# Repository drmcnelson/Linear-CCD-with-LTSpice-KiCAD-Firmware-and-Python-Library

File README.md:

# Linear-CCD-with-LTSpice-KiCAD-Firmware-and-Python-Library
by Dr M C Nelson (C) 20220-2026 [(the authoritative repo is here)](https://github.com/drmcnelson/Linear-CCD-with-LTSpice-KiCAD-Firmware-and-Python-Library)

<br>

> **Note:** For the **high-linearity version** for quantitative science along with a revised implementation of this all-in-one design but now with hardware locked timing (using the FlexPWM), please see the newer repository: [TCD1304-Sensor-Device-with-Linear-Response-and-16-Bit-Differential-ADC](https://github.com/drmcnelson/TCD1304-Sensor-Device-with-Linear-Response-and-16-Bit-Differential-ADC).

<br>

## Introduction
Linear CCDs can be useful tools in science, for example as a sensor for a spectrometer or imaging system.  And indeed, there are many commercial instruments that are based on low cost linear CCDs such as the Toshiba TC1304 and the Sony IXL511.
Here we provide design files, firmware and software for a device that provides competitive performance and a rich set of science-centric features, and that can be customized to your experiments, all at a fraction of the cost of the commercial offerings.  The design is based on the Toshiba TCD1304 (3648/3694 pixels) and Teensy 4.0 (600MHz ARM, 480MHz USB).  The Teensy 3.2 is plug compatible for this design.
Read further below, and you will find tutorials on electrical design and managing the CCD to provide flexible timing and reproducible measurements so that you can use it as a scientific instrument.

In this repository you will find directories containing (a) electrical design files in KiCad, (b) firmware (a sketch file) for the Teensy, and (c) a Python class library with graphical and command line utilities to operate the device.
The device has a trigger or gate input, sync and busy outputs, and spare pins for digital and analog I/O.
The operating modes include clocked, triggered frames, triggered series of frames, and gated frames (where the shutter is opened and closed on the rising and falling edges of the logic level input signal).
The device appears as a serial port (COM in windows) with comands and response in human language ASCII and frames returned as binary or formatted.
The python class library provides higher level functions, a graphical realtime display and a command line processor.  There is a help command in the firmware and in the Python command line interpreter.  Details of the electrical and firmware design are described later in this README.

The following shows the microcontroller side of the device.  The sensor side can be seen in the image of the spectrometer (below).   The digital I/O pins across the top include trigger input, sync and busy output, pins that monitor the signals going to the sensor, and spares that can be controlled through the user interface.  Across the bottom there are pins that can be used for analog inputs or digital I/O, and 3.3V that can be used for an auxiliary device.

Following are two examples of applications; using the sensor in a spectrometer and measurement of spectral-spatial-dynamics in an OLED.  This repository provides what you need in terms of ecad files and software to build one for yourself, or if you like you can contact me for an assembled board.

The files in the repo were produced on a Linux desktop computer (Fedora 37, Cinnamon Spin), using KiCAD 6 for the electrical design and Emacs for the firmware and python programs.

<ul>
 <i>
For next level designs and a preview of our study on linearity and reproducibility in CCDs see our new repo at <a href=https://github.com/drmcnelson/TCD1304-Sensor-Device-with-Linear-Response-and-16-Bit-Differential-ADC>TCD1304 with linear response and 16bit ADC</a>. We suggest perusing both this and the new repo and selecting the implementation that best serves your needs.  Feel free to contact me with questions.
 </i>
</ul>

## Some Example Use Cases

### Spectrometer
The first shows the inside of a spectrometer built with a G1200 grating, two lenses and a slit. The mounts are 3D printed and everything is affixed to a stiff Al plate. There is a cover, not shown here, and specific surfaces are covered with low-reflectance tape.  The spectrum is that of a fluorescent ceiling light through a 200um fiber at a distance of about 8ft, with a 200um slit.

|||

### Imaging Spectral-Spatial-Dynamics
The following example uses the sensor device to record the time evolution of the spatial distribution of light produced by an OLED at a current density of 150 $\mu A/cm^2$. The sensor device collects a series of frames wth 10ms shutters at 10ms intervals (back to back), with the series initated on a trigger at the start of the applied voltage waveform. The blue line shows the resulting current density in the OLED, the pale line shows the sync pulses output by the sensor device at the start of each frame, and the red line is the applied voltage (2.41V).  (We plan to post repositories for the DAQ board and current amplifier as well.)

|||

# Electrical Design, Analog
The datasheet for the TCD1304 can be found here  https://toshiba.semicon-storage.com/us/semiconductor/product/linear-image-sensors/detail.TCD1304DG.html.
The following table is found on page 4.
We see that $V_{SAT}$ the saturation output volage runs from 450mV to 600mV, $V_{MDK}$ the dark signal is 2mV, thus a dynamic range of 300 (for a 10ms integration integral), $V_{OS}$ the DC output signal is typically 2.5V but can be from 1.5V to 3.5V, and $Z_O$ the output impedance is typically 500 ohms but can be 1K.  So, that is a lot of variation that we need to account for in our design.

The datasheet provides the following diagram in Note 8 to illustrate the definition of $V_{OS}$.  The hatched area is the negative going output signal.  SS is ground

For best performance in digitizing the signal, we want a circuit that takes the above signal as input and outputs a signal that matches the input range of our microcontroller's ADC.  The following circuit element shows one approach that does this and can run on a single supply. We can call this a shift, flip and amplify (SFA). The gain is set as usual for an inverting amplifier by $R_2$ and $R_1$ and the potentiometer provides the offset through the + input of the opamp.

But, recall that the datasheet says the output impedance $Z_0$ varies from 500 ohms to 1k.  If we connect that directly to our SFA then $Z_0$ becomes part of the gain equation, $R1\rightarrow R1+Z_0$, and in a bag of sensors we might find that the gain is different for each sensor.
So, we need to isolate that source impedance from the SFA.

A solution to this is to use an opamp follower as the first stage, as shown in the following crcuit.  The follower presents a very high impedance at its input, which is ideal for reading the voltage from the sensor, and a low impedance at its output, which is ideal as an input to the SFA

Referring again to the datasheet for the TCD1304, we see that (a) we can operate the sensor chip in the range 3V to 5.5V, (b) it requires a clock between 800KHz and 4MHz (2MHz if operated below 4V) and (c) the data readout rate is 1/4 of the clock 200kS/s to 1MS/s (500KS/S if powered below 4V).
Operating with a 3.3V supply, and making efficient use of the full scale range of the ADC,  means that we need to use a rail to rail opamp.
Our SFA architecture means that the opamp has to also have a wide common mode range. 
And the sampling rate means we need to look for a slew at least as faster as 100V/usec

The complete analog front end circuit is shown in the following LTSpice model based on the ADA4807.
We use the first opamp in the package for the voltage follower and the second opamp for the flip, shift,and amplify stage.
Gain and offset are as calculated above.
The green trace is the output from the sensor and the purple curve is the output from the second stage.
As can be seen the 2.5V to 1.9V signal from the sensor becomes a 0.1V to 3.1V for the ADC, and the rise time is small compared to the sampling period.
In our actual circuit we use a trim pot for the voltage applied to V+.

It might be noted that we could have chosen a larger gain to look at lower intensity light, or with the Teensy 3.2 we can use its built-in amplifier under software control, provided the offset is small.

## Analog input of the Teensy 4.x and Teensy 3.2
The following diagaram for the analog input, and one similar to this, are found in the datasheets for the i.MXRT106x (Teensy 4) and the K20 (Teensy 3).
This is a modified version of a SAR type analog input.  Normally the input sees the switched sampling capacitor.
Here there is a series resistor in front of the sampling capacitor.

In operation, the switch closes for a period of time to allow the capacitor to draw charge from the input.
At the end of the sampling period the switch is opened and the voltage on the capacitor is converted to a digital representation in the successive approximation register (SAR).
In other words, precision is determined by the length of the sampling window (in time) versus the RC time constant seen by the sampling capacitor.
Full precision means the voltage on the capacitor is within 1 LSB of the input, at the end of the sampling window.

For a simple RC network, the voltage on the capacitor is $V(t)/V(0) = 1 - exp(-t/RC)$.
Therefore, for n bits of precision, the sampling window needs to be at least $ln(2^{n}) \times RC$.
This works out to be 11 x RC for 16 bits and 8 x RC for 12 bits. 
The following shows this graphically.

For the T3 in 16 bit mode, with RADIN = 2k, and CADIN = 8pf, RC ~ 16nsecs.
The voltage on the sampling capacitor is within $1/2^{16}$ of the input voltage after about 170nsecs.

For the T4 in 12 bit mode, RADIN can be from 5k to 25k and CADIN is 1.5pF, RC ~ 7.5nsecs to 40nsecs.
We need about 60nsecs to 320nsecs to reach 12 bit precision.

Thus the T3 and T4 are both compatible at 500KSPS.  See the [ADC library](https://github.com/pedvide/ADC) for details setting the sampling time and conversion clock.

The tradeoff for the T3 with its 16 bit input, is that the T3 has a much slower USB interface, 1MB/s transfers to the host versus 60MB/s for the T4.
The best frame to frame interval with the T3 is about 16msecs and about 8msecs for the T4.

N.B.  Driving the analog input of an MCU is different from driving a normal SAR type ADC.  Normally, the drive circuit for a SAR includes an external capacitor to serve as a charge reservoir for the sampling capacitor.  This is pre-empted in the MCU analog input by the large internal resistance in series with the sampling capacitor.

## How many bits do I really need?
In the table above, the dynamic range is listed as 300.
This is simply the saturation output voltage 600mv divided by the dark signal 2mV.
If that were the limit, then 10 good bits would be enough.

In principle the dark noise should scale with exposure time or by cooling.  Emperically, using a special low noise linear radiometric design(*), we find that the noise floor for the TCD1304 seems to be at about 0.6mV which it reaches for exposures below about 10msec.  Modest cooling to 4C is reported elsewhere to reduce noise by a factor of 4.  So, we can estimate a practical limit for the dynamic range at about 4,000, or 12 bits.  That is what is offered by the T4 ADC.  If you want to do signal averaging, and given the usual performance specs of ADCs, it is reasonable to have some extra bits, and so a 16 bit ADC is a good choice for a high performance system.

Our analog section uses an ADA4807.  Its datasheet lists the input voltage noise as $3.1 nV/\sqrt Hz$.
At 500KSPS this becomes 2.2uV, and setting the gain at 5, we expect 10uV.  So, we are well ahead of the noise floor for the device.
Without going into a more detailed analysis, we see that our electrical noise can be about 1/2 of the dark signal.
That is workable with some signal averaging.

(*) Our high performance designs with differential signal paths and ADC are posted at
[TCD1304 Sensor Device with Linear Response and 16 bit Differential ADC](https://github.com/drmcnelson/TCD1304-Sensor-Device-with-Linear-Response-and-16-Bit-Differential-ADC)
and
[S11639-01 with 16 bit differentual ADC for SPI](https://github.com/drmcnelson/S11639-01-Linear-CCD-PCB-and-Code).
 Both of these have been built and tested and the repos now have all of the gerbers, bom, firmware and user code.
We plan to upload a repo with a cooled sensor in the near future.   The other advantage of those designs is that they are two board systems and provide better mechanical isolation if your are changing cables after alignment.  But, the design posted here offers sufficient precision and has fewer parts (i.e., it costs less and takes less time to build).

# CCD operation
Operationally, a CCD sensor stores charge in each pixel proportional to light and noise, until assertion of a shift pin causes the contents to be transferred to a buffer and then the contents are shifted along the buffer by a clock to the output pin and appear as a series of voltages.
The TCD1304 has an additional function that controls which shift assertions initiate the readout sequence.
The internal structure is depicted as follows from page 3 of its datasheet.  Externally the device is controlled by three pins, shift SH, integration clear gate ICG, and master clock $\phi M$.

The following two figures from the datasheet show how Toshiba envisions operation of the sensor chip.  As indicated, charge is integrated during the intervals between trailing edges at the SH pin. When the the ICG pin is low the accumulated charges are available in the readout buffer and then shifted to the output pin at a rate of 1 datum per four cycles of the master clock.

Toshiba labels the second diagram above as "Electronic Shutter Function".  This refers to the function of ICG in selecting which SH assertion results in charge being available in the readout buffer.  However it is not a shutter in the conventional sense.  It is easily shown experimentally that if the device is left idle, several SH cycles are needed to arrive at a noise level baseline in the readout.   There are a number of commerical CCD systems that clock the SH pin or its equivalent to keep the sensor "clean".  This can have important ramifications if the device is to be triggered, for example for kinetic studies.   Alternatives include good "dark" management, designing the experiment to start with a few blank frames to clear the sensor, and/or having the device initiate the trigger.

Note that it is the low state on the ICG pin that makes the readout available to be clocked out to the OS pin, while the SH pin sets the integration interval.

## Driving the SH, ICG and Master Clock pins
Referring again to the datasheet, page 6, we find the following table.
Notice that the shift gate has a capacitance of 600pF and the integration clear gate has 250pF.
From the magnitude of the capacitances, we might guess that these are closely related to moving charge to the output buffer.

Notice also, that the master clock and data transfer rates are reduced when operating at lower voltages.

The large capacitances also factor into how we drive these pins, rise times with large capacitances are easily current limited.
The preferred way to drive the gate pins is with a buffer and series resistor, as shown in the following.
For a 3.3V drive, a 150 ohm resistor sets the rise to 90nsecs for the SH pin and limits the current to 22mA.
For a 1 usec pulse, this gives a rise time that is less than 1/10 of the pulse width.
The buffer can be a 74LVC1G34, or one channel of a 74VLC3G34, which can drive 25mA.

For comparison, the Teensy digital I/O pins provide 4mA.
If the gate is driven directly from the Teensy, the response is current limited, $\Delta t \approx C \Delta V / I$.
That works out to 500nsecs.
So, driving the gates from the digital I/O pins can work, if you can accomodate the longer pulse duration needed for the current limited pulse rise time.

In this repo we provide two sub-directories for designs for the all-in-one TCD1304 and Teensy, with and without the 25mA pulse driver (74VLC3G34).  The verion with 25mA gate drivers is the preferred version.  The KiCad files for that version are [here](TCD1304Rev2GDKiCAD).

For our high-end board with 16 bit ADC and faster timing, see our repo .

## Frame rates, shutters and timing for data acquisition.
The following diagram from page 9 of the datasheet shows the timing requirements for the ICG and SH pins relative to each other and the master clock.

With a 2MHz master clock, it takes about 7.4ms to read one record from the device into the memory of the microcontroller.  Transfer from the microcontroller to the host PC can take an additional 5ms for the Teensy 3.x (12 Mb/s) or about 120usec with the Teensy 4.x (480 Mb/s).  Needless to say, this sets the maximum frame rate, that is the time between readouts, and is different from the minimum integration interval which depends only on the minimal interval between successive trailing edges at the SH pin.

For data collection, we need to be able to set integration and frame intervals freely (within the physical limits of the sensor) and we need to be able to reliably control timing with respect to an external trigger or gate.   Since the shutter or integration interval is defined by successive assertions of the SH pin, we focus on how these requirements translate to operation of this pin.

The following diagram shows a sequence where the shutter interval is shorter than the inter frame interval, and the frame interval is not necessarily an integer number of shutter intervals in length.  The SH pin operates with alternating short and long intervals.  The frame interval is the sum of these two intervals, or that betwen every second SH.

The following shows back to back shutters with identical frame and shutter intervals.

And this one shows a constant shutter interval with the frame interval an integer multiple of the shutter.

Our control logic for operating the device has to accomodate all three scenarios, and we have to be able to initiate frames or sets of frames from a clock or from a trigger.
Architecturally, we set this up as two ISRs, which we call ShutterA_isr() and ShutterB_isr().  The sequences are easily implemented by various combinations of A and B or just B after one A, and easily triggered, gated or clocked as needed.

## Signals, Sync and Busy
The sensor device has a trigger input and two outputs SYNC and BUSY.  Sync can be configured to signal the start of a series of frames or to signal the start of each shutter.  SYNC can also be configured to be followed by a holdoff.  BUSY is set with the start of the first shutter and remains asserted until the last data transfer is complete.   Each pin can be set nominally HIGH or LOW, assertion is the opposite.  Additionally there is a SPARE pin.  Any of the pins can be manually set, cleared, toggled or pulsed.

The following shows the actual operation of the sensor device, green is SH, purple is ICG, blue is SYNC and yellow is BUSY.  We see BUSY goes high immediately, SH and ICG operate as described in the data sheet.  Light is integrated between the two trailing edges and the data is transferred following the second assertion of the SH and clearing of the ICG pins.

## Triggered and gated operation
The following shows a triggered frame.  The commands are "set trigger rising", "trigger 20" to trigger one 20usec frame.  The blue line is the trigger input.  There is a small reproducible delay between the trigger and the shutter, due to certain fixed timings involved in getting the shutter started.  Notice the alignment of the BUSY and SH signals.

The following shows a gated frame, blue is the gate signal.  The commands are "set trigger change", "gate 1", to gate one frame.  For this, the spare pin is connected to the trigger input and we enter the command "pulse spare 20" to output a 20 usec pulse.  As you can see the shutter sequence begins and finishes with the gate.

# Data processing
Referring to the clock diagrams above, we see that the data record comprises 12 dummy outputs followed by 13 light shielded elements, followed by 3 shadowed elements, followed by the 3648 elements making up the effective output and followed by another 14 dummy elements.   Thus elements 12 thru 24 provide a baseline which we can average or take the median and subtract from elements 28 through 2675 which form the image.   In the spirit of "always preserve primary data", we do not do this substraction nor any scaling, in firmware.  Rather we pass the entire record as is, to the PC host and the host software is responsible for subtracting and scaling as appropriate.

# Firwmare
The firmware subdirectory contains a sketch for Teensy 4.0.  After assembling your board (or obtaining one from the author), you can mount your Teensy 4 and TCD1304 detector, and then flash the program into the Teensy 4.0.   The commands are in english, ASCII over USB.  Enter the command "help" to get a listing and short explanation of the commands.  A listing of the help text is included in the Python subdirectory.

The default action returns the data in binary.  You will ideally want to use a multi-threaded program on your host computor, with one thead reading the responses and data and queuing as appropriate to a separate graphics thread.   The Python code provides a Class for the device that handles all of this.

# Python
The Python subdirectory contains a file TCD1304Rev2Controller.py and three library files that it looks for in its directory.  The program implements threads using the multitasking interface in Linux.  A dedicated thread reads the responses from the device and queues data to an internal data queue for the "save" command and to a queue read by the runtime graphics thread.  The Python program has a help command, like the firmware.

# Adjusting the offset
With a voltmeter or scope, the middle pin on the trim pot should be set close to 2.1 volts.  Then in the Python program, issue the commands "baseline off" and "clock 1000 10000 100000".   This wil turn off the baseline subtraction function and clock 1000 frames with an integration time of 10ms spaced at intervals of 100ms.   Try the commands "stop", "baseline on" and repeat the clock command to see a comparison.  You can zoom in on the graphical display and use a small screwdriver to adjust the offset.   I usually put the sensor in a drawer or cover it with a black cloth while I do this.

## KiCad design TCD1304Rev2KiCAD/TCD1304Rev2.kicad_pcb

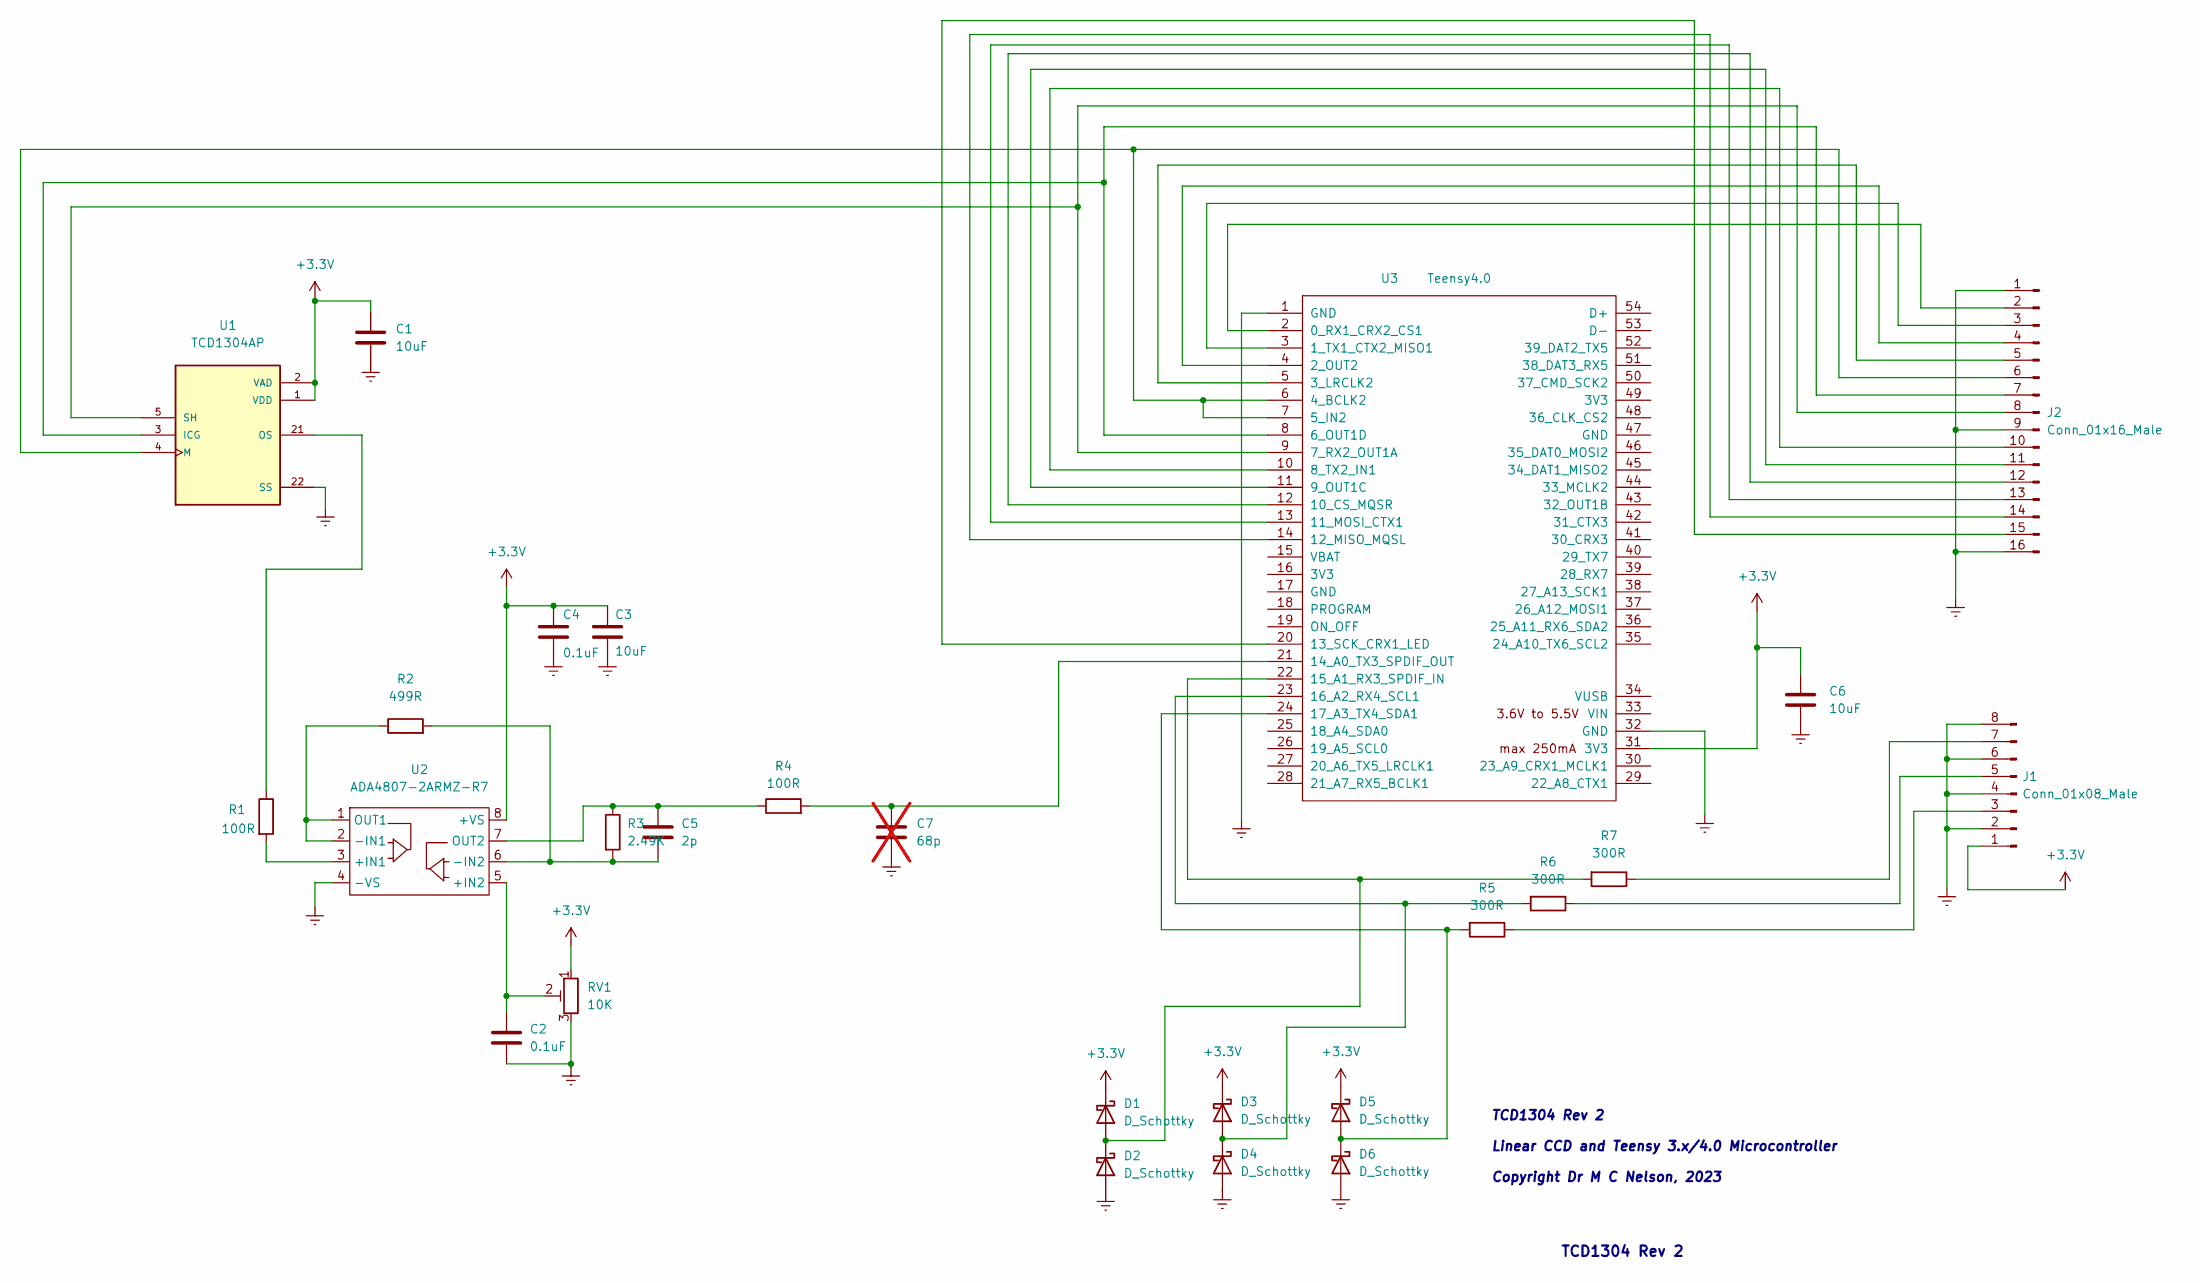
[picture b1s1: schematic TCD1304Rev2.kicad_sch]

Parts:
C1, C3, C6: 10uF; C_0603_1608Metric; Digikey 490-12317-1-ND
C2, C4: 0.1uF; C_0603_1608Metric; Digikey 399-C0603X104J3RACAUTOCT-ND
C5: 2p; C_0603_1608Metric; Digikey 1284-1196-1-ND
C7: 68p; C_0603_1608Metric; Digikey 1276-1135-1-ND; not fitted
D1, D2, D3, D4, D5, D6: D_Schottky; D_SOD-323; Digikey CUS520H3FCT-ND
J1: Conn_01x08_Male; PinHeader_1x08_P2.54mm_Vertical; Digikey 3M156268-08-ND
J2: Conn_01x16_Male; PinHeader_1x16_P2.54mm_Vertical; Digikey 3M156268-16-ND
R1, R4: 100R; R_0603_1608Metric; Digikey 2019-RK73H1JTTD1000FCT-ND
R2: 499R; R_0603_1608Metric; Digikey 2019-RK73H1JTTD4990FCT-ND
R3: 2.49K; R_0603_1608Metric; Digikey 311-2.49KHRCT-ND
R5, R6, R7: 300R; R_0603_1608Metric; Digikey 2019-RK73H1JTTD3000FCT-ND
RV1: 10K; TRIM_3296W-1-502LF; Digikey 3296W-103LF-ND
U1: TCD1304AP; DIP1016W47P254L4210H372Q22; Digikey 110-87-422-41-001101
U2: ADA4807-2ARMZ-R7; MSOP-8_3x3mm_P0.65mm; Digikey ADA4807-2ARMZ-R7CT-ND
U3: Teensy4.0; Teensy40; Digikey 1568-DEV-16997-ND

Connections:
+3.3V: C1.1, C3.1, C4.1, C6.1, D1.1 (K), D3.1 (K), D5.1 (K), J1.1, RV1.1, U1.1 (VDD), U1.2 (VAD), U2.8 (+VS), U3.31 (3V3)
Earth: C1.2, C2.2, C3.2, C4.2, C6.2, C7.2, D2.2 (A), D4.2 (A), D6.2 (A), J1.2, J1.4, J1.6, J1.8, J2.1, J2.9, J2.16, RV1.3, U1.22 (SS), U2.4 (-VS), U3.1 (GND), U3.32 (GND)
unnamed: D1.2 (A), D2.1 (K), R7.2, U3.22 (15_A1_RX3_SPDIF_IN)
unnamed: D3.2 (A), D4.1 (K), R6.2, U3.23 (16_A2_RX4_SCL1)
unnamed: D5.2 (A), D6.1 (K), R5.2, U3.24 (17_A3_TX4_SDA1)
unnamed: J1.3, R5.1
unnamed: J1.5, R6.1
unnamed: J1.7, R7.1
unnamed: J2.2, U3.2 (0_RX1_CRX2_CS1)
unnamed: J2.3, U3.3 (1_TX1_CTX2_MISO1)
unnamed: J2.4, U3.4 (2_OUT2)
unnamed: J2.5, U3.5 (3_LRCLK2)
unnamed: J2.6, U1.4 (M), U3.6 (4_BCLK2), U3.7 (5_IN2)
unnamed: J2.7, U1.3 (ICG), U3.8 (6_OUT1D)
unnamed: J2.8, U1.5 (SH), U3.9 (7_RX2_OUT1A)
unnamed: J2.10, U3.10 (8_TX2_IN1)
unnamed: J2.11, U3.11 (9_OUT1C)
unnamed: J2.12, U3.12 (10_CS_MQSR)
unnamed: J2.13, U3.13 (11_MOSI_CTX1)
unnamed: J2.14, U3.14 (12_MISO_MQSL)
unnamed: J2.15, U3.20 (13_SCK_CRX1_LED)
unnamed: R1.1, U1.21 (OS)
unnamed: R1.2, U2.3 (+IN1)
unnamed: C2.1, RV1.2, U2.5 (+IN2)
unnamed: R2.1, U2.1 (OUT1), U2.2 (-IN1)
unnamed: C5.2, R2.2, R3.2, U2.6 (-IN2)
unnamed: C5.1, R3.1, R4.1, U2.7 (OUT2)
unnamed: C7.1, R4.2, U3.21 (14_A0_TX3_SPDIF_OUT)

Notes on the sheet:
TCD1304 Rev 2 Linear CCD and Teensy 3.x/4.0 Microcontroller Copyright Dr M C Nelson, 2023
TCD1304 Rev 2

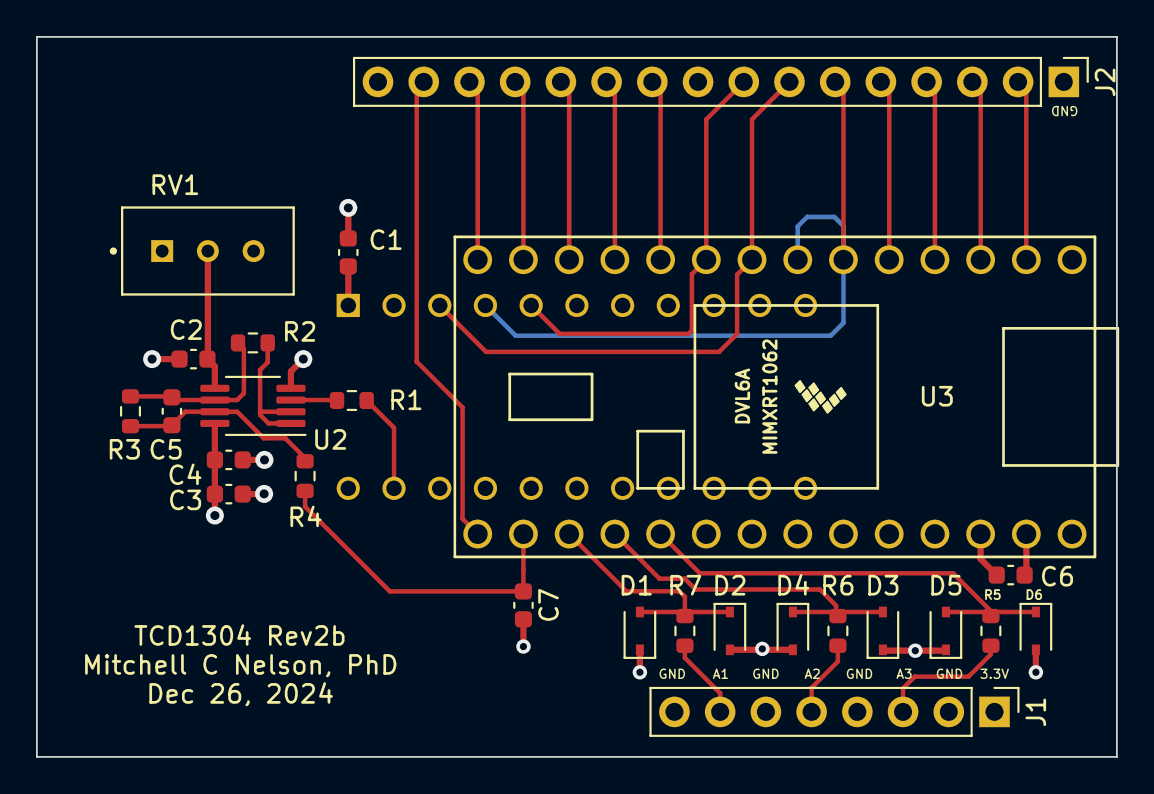
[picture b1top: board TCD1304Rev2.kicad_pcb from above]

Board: 4 copper layers, 60.0 x 40.0 mm, 26 parts (1 on the bottom side), 28 nets.

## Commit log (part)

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2023-12-18 KiCAD files for TCD1304 Rev2
    These are the KiCAD project, schematic and pcb files.
2023-12-18 LTSpice file for the sensor and front end circuit
    LTSpice model for the sensor and front end circuit.
2023-12-18 Python Controller Program and Class Library
    Python controller program and class library for the TCD1304Rev2b firmware
2023-12-18 TCD1304Rev2 KiCAD files
2024-02-07 Update TCD1304Rev2b_Firmware.231218.ino
    Add to the comment for the clock monitor pin
2024-03-01 Maintenance update
2024-12-24 Correction
    C7 should be 68p and DNP (do not populate). Normally, for a SAR type input, best results are obtain with an external resistor and capacitor to act as a charge reservoir for the sampling capacitor. Bu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
2024-12-24 Expand explanation of the front end circuit
2024-12-24 Add discussion on driving the gate pins
    The gate pins function in moving charge from the sensing elements to buffer and then to the readout buffer.
2024-12-24 minor editorial changes
2024-12-24 All-in-One TCD1304 update, with gate drivers
    This version uses a 74LVC3G34 to drive the SH, ICG and master clock pins.
2024-12-24 Discussion of the analog input in the T4 and T3
2024-12-24 Discusses analog inputs, when to use 16 bits and upcoming cooled sensors
2024-12-25 More detail on the analog interface and driving the gates
2024-12-26 Minor changes (best practice update)
2025-08-07 Correct footprint for U4 (74LVC3G34)
    With apologies, this update corrects the footprint for the 74LVC3G34, to match that for the part listed in the schematic BOM, the NXP 74LVC3G34DP,125, Digikey part number 1727-6685-1-ND.
    The KiCAD footprint library contains two versions of TSSOP-8, size 4.4mm and 3.3m. This part matches the smaller TSSOP-8.
2025-08-19 Delete TCD1304Rev2c_KiCAD directory
    this version in testing, to be restored later
2025-08-19 Update README.md
    Update for noise measurements and current designs
2025-10-01 Minor edits
2025-11-10 All In One TCD1304 with buffer gate driver
2026-01-21 Create LICENSE
